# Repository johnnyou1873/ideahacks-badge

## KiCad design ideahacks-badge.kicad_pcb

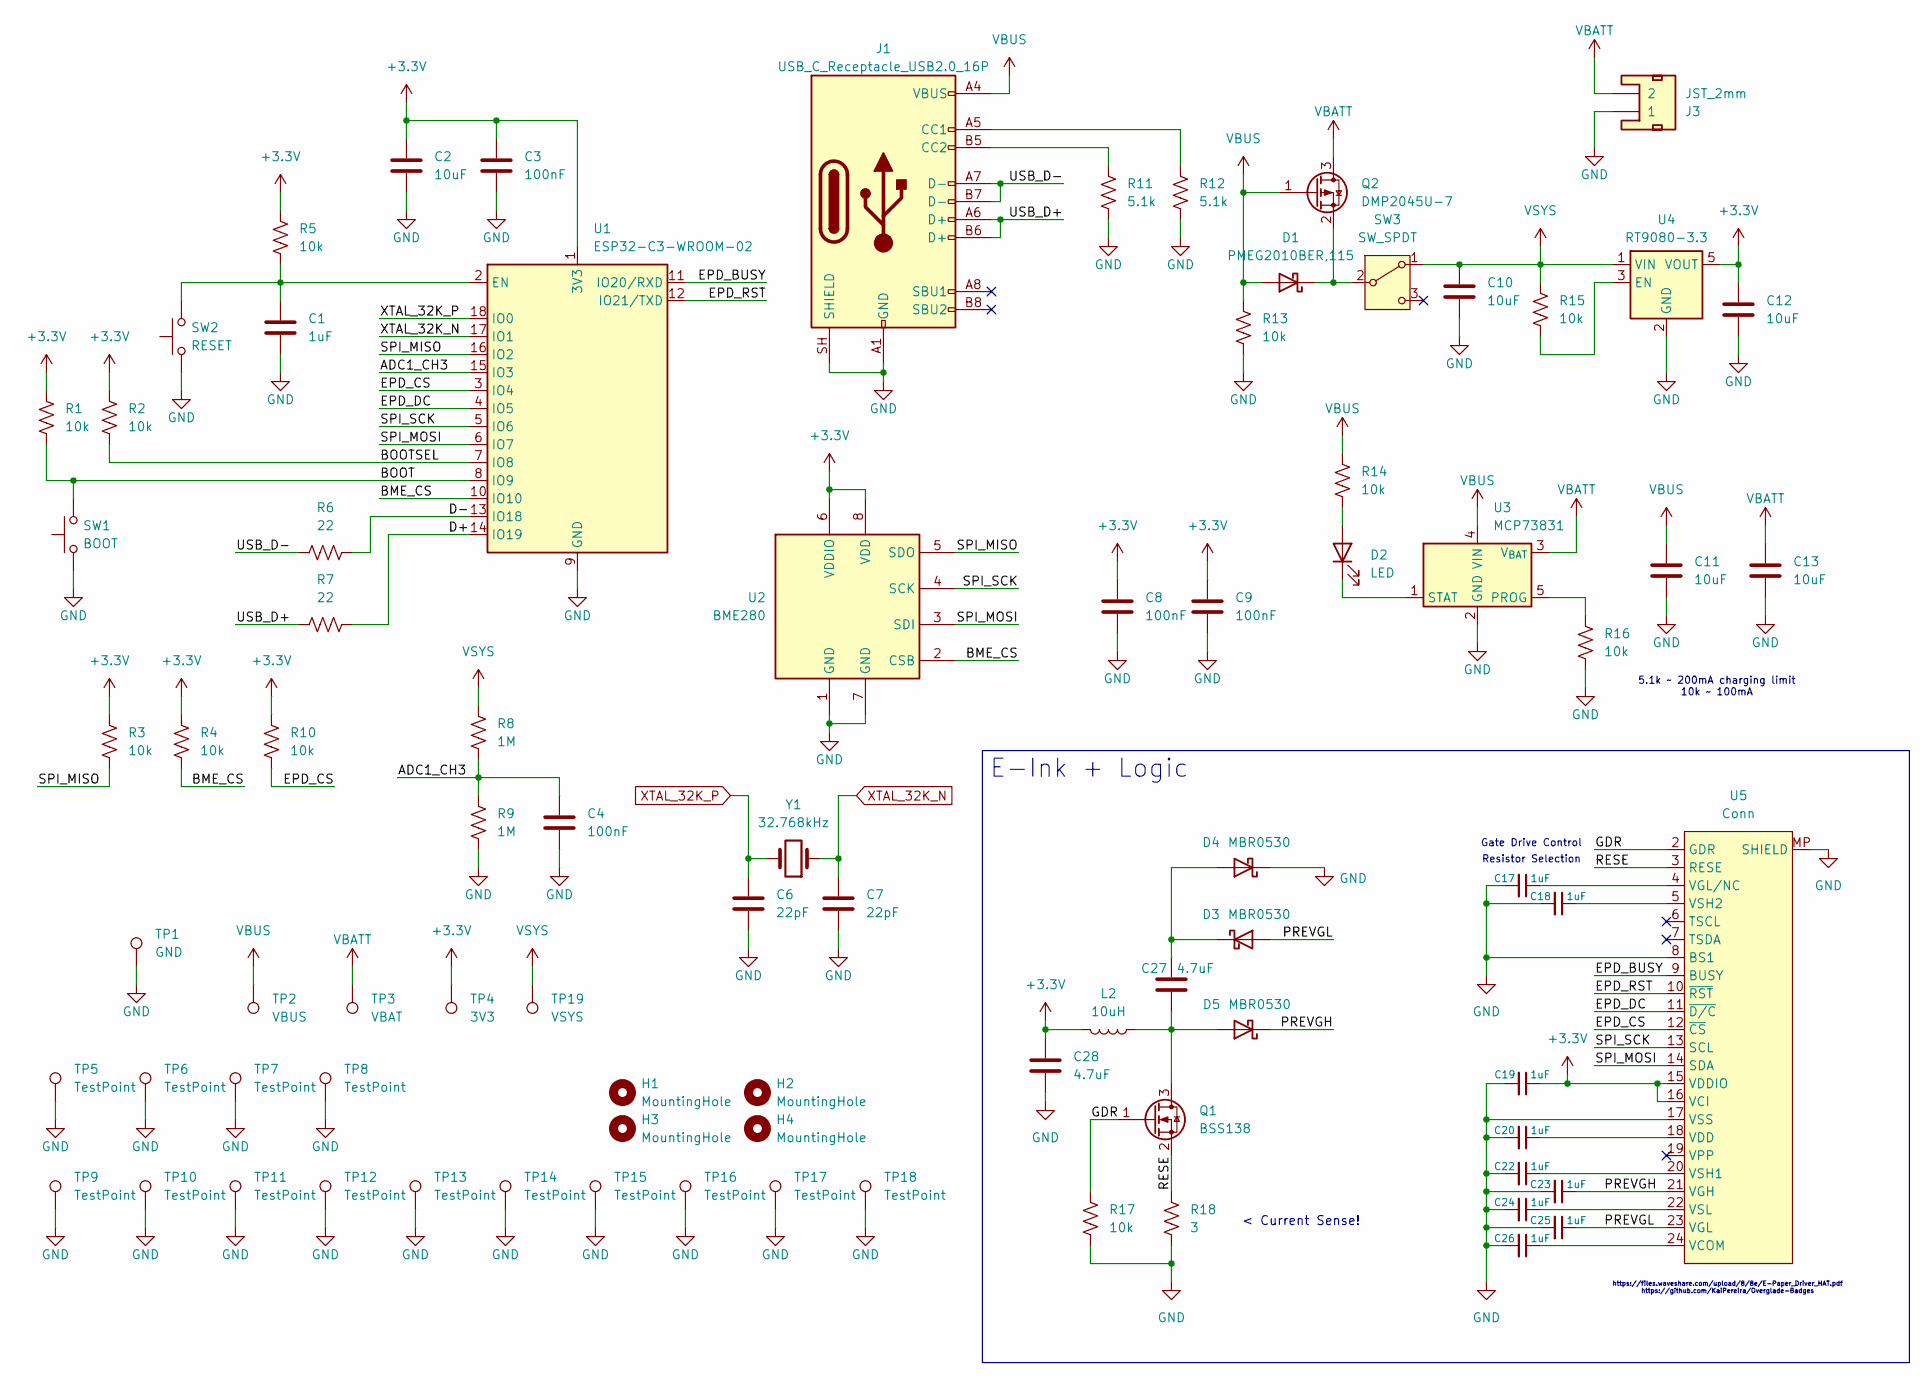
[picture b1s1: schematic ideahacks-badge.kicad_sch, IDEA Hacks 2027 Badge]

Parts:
C1, C17, C18, C19, C20, C22, C23, C24, C25, C26: 1uF; C_0805_2012Metric_Pad1.18x1.45mm_HandSolder
C2, C10, C11, C12, C13: 10uF; C_0805_2012Metric_Pad1.18x1.45mm_HandSolder
C3, C4, C8, C9: 100nF; C_0805_2012Metric_Pad1.18x1.45mm_HandSolder
C6, C7: 22pF; C_0805_2012Metric_Pad1.18x1.45mm_HandSolder
C27, C28: 4.7uF; C_0805_2012Metric_Pad1.18x1.45mm_HandSolder
D1: PMEG2010BER,115; Nexperia_CFP3_SOD-123W
D2: LED; LED_0805_2012Metric_Pad1.15x1.40mm_HandSolder
D3, D4, D5: MBR0530; D_SOD-123
H1, H2, H3, H4: MountingHole; MountingHole_3.2mm_M3_Pad
J1: USB_C_Receptacle_USB2.0_16P; USB_C_Receptacle_HRO_TYPE-C-31-M-12
J3: JST_2mm; JST_1x02_P2.0mm_Horizontal_PTH
L2: 10uH; L_Changjiang_FNR6028S; MPN FNR6028S680MT
Q1: BSS138; SOT-23_Handsoldering
Q2: DMP2045U-7; SOT-23_Handsoldering
R1, R2, R3, R4, R5, R10, R13, R14, R15, R16, R17: 10k; R_0805_2012Metric_Pad1.20x1.40mm_HandSolder
R6, R7: 22; R_0805_2012Metric_Pad1.20x1.40mm_HandSolder
R8, R9: 1M; R_0805_2012Metric_Pad1.20x1.40mm_HandSolder
R11, R12: 5.1k; R_0805_2012Metric_Pad1.20x1.40mm_HandSolder
R18: 3; R_0805_2012Metric_Pad1.20x1.40mm_HandSolder
SW1: BOOT; SW_PUSH_6mm
SW2: RESET; SW_PUSH_6mm
SW3: SW_SPDT; SW_SLW-864574-5A-RA-N-D
TP1: GND; TestPoint_Pad_D2.0mm
TP2: VBUS; TestPoint_Pad_D2.0mm
TP3: VBAT; TestPoint_Pad_D2.0mm
TP4: 3V3; TestPoint_Pad_D2.0mm
TP5, TP6, TP7, TP8, TP9, TP10, TP11, TP12, TP13, TP14, TP15, TP16, TP17, TP18: TestPoint; TestPoint_Pad_D2.0mm
TP19: VSYS; TestPoint_Pad_D2.0mm
U1: ESP32-C3-WROOM-02
U2: BME280; Bosch_LGA-8_2.5x2.5mm_P0.65mm_ClockwisePinNumbering
U3: MCP73831; SOT23-5
U4: RT9080-3.3; SOT23-5
U5: Conn; Amphenol_F32Q-1A7x1-11024_1x24-1MP_P0.5mm_Horizontal; LCSC Part # C262567
Y1: 32.768kHz; Crystal_C26-LF_D2.1mm_L6.5mm_Horizontal

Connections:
+3.3V: C2.1, C3.1, C8.1, C9.1, C12.1, C19.1, C28.2, L2.2, R1.1, R2.2, R3.1, R4.2, R5.2, R10.2, TP4.1 (1_1), U1.1 (3V3), U2.6 (VDDIO), U2.8 (VDD), U4.5 (VOUT), U5.15 (VDDIO), U5.16 (VCI)
/ADC1_CH3: C4.2, R8.2, R9.2, U1.15 (IO3)
/BME_CS: R4.1, U1.10 (IO10), U2.2 (CSB)
/BOOT: R1.2, SW1.2, U1.8 (IO9)
/BOOTSEL: R2.1, U1.7 (IO8)
/D+: R7.1, U1.14 (IO19)
/D-: R6.1, U1.13 (IO18)
/EPD_BUSY: U1.11 (IO20/RXD), U5.9 (BUSY)
/EPD_CS: R10.1, U1.3 (IO4), U5.12 (~CS)
/EPD_DC: U1.4 (IO5), U5.11 (~D/C)
/EPD_RST: U1.12 (IO21/TXD), U5.10 (~RST)
/GDR: Q1.1 (G), R17.1, U5.2 (GDR)
/PREVGH: C23.1, D5.1 (K), U5.21 (VGH)
/PREVGL: C25.1, D3.2 (A), U5.23 (VGL)
/RESE: Q1.2 (S), R18.1, U5.3 (RESE)
/SPI_MISO: R3.2, U1.16 (IO2), U2.5 (SDO)
/SPI_MOSI: U1.6 (IO7), U2.3 (SDI), U5.14 (SDA)
/SPI_SCK: U1.5 (IO6), U2.4 (SCK), U5.13 (SCL)
/USB_D+: J1.A6 (D+), J1.B6 (D+), R7.2
/USB_D-: J1.A7 (D-), J1.B7 (D-), R6.2
GND: C1.2, C2.2, C3.2, C4.1, C6.1, C7.1, C8.2, C9.2, C10.2, C11.2, C12.2, C13.2, C17.2, C18.2, C19.2, C20.2, C22.2, C23.2, C24.2, C25.2, C26.2, C28.1, D4.1 (K), J1.A1 (GND), J1.A12 (GND), J1.B1 (GND), J1.B12 (GND), J1.SH (SHIELD), J3.1, R9.1, R11.2, R12.2, R13.2, R16.2, R17.2, R18.2, SW1.1, SW2.1, TP1.1 (1_1), TP5.1 (1_1), TP6.1 (1_1), TP7.1 (1_1), TP8.1 (1_1), TP9.1 (1_1), TP10.1 (1_1), TP11.1 (1_1), TP12.1 (1_1), TP13.1 (1_1), TP14.1 (1_1), TP15.1 (1_1), TP16.1 (1_1), TP17.1 (1_1), TP18.1 (1_1), U1.9 (GND), U1.19 (GND), U2.1 (GND), U2.7 (GND), U3.2 (GND), U4.2 (GND), U5.8 (BS1), U5.17 (VSS), U5.MP (SHIELD)
unnamed: D1.1 (K), Q2.2 (S), SW3.2 (B)
unnamed: D2.2 (A), R14.2
unnamed: D2.1 (K), U3.1 (STAT)
unnamed: C27.2, D3.1 (K), D4.2 (A)
unnamed: C27.1, D5.2 (A), L2.1, Q1.3 (D)
unnamed: J1.A5 (CC1), R12.1
unnamed: J1.B5 (CC2), R11.1
unnamed: C1.1, R5.1, SW2.2, U1.2 (EN)
unnamed: R16.1, U3.5 (PROG)
unnamed: R15.2, U4.3 (EN)
unnamed: C26.1, U5.24 (VCOM)
unnamed: C20.1, U5.18 (VDD)
unnamed: C17.1, U5.4 (VGL/NC)
unnamed: C22.1, U5.20 (VSH1)
unnamed: C18.1, U5.5 (VSH2)
unnamed: C24.1, U5.22 (VSL)
VBATT: C13.1, J3.2, Q2.3 (D), TP3.1 (1_1), U3.3 (V_{BAT})
VBUS: C11.1, D1.2 (A), J1.A4 (VBUS), J1.A9 (VBUS), J1.B4 (VBUS), J1.B9 (VBUS), Q2.1 (G), R13.1, R14.1, TP2.1 (1_1), U3.4 (VIN)
VSYS: C10.1, R8.1, R15.1, SW3.1 (A), TP19.1 (1_1), U4.1 (VIN)
XTAL_32K_N: C7.2, U1.17 (IO1), Y1.1
XTAL_32K_P: C6.2, U1.18 (IO0), Y1.2

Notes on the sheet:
5.1k ~ 200mA charging limit 10k ~ 100mA
https://files.waveshare.com/upload/8/8e/E-Paper_Driver_HAT.pdf https://github.com/KaiPereira/Overglade-Badges
Resistor Selection
Gate Drive Control
< Current Sense!
E-Ink + Logic

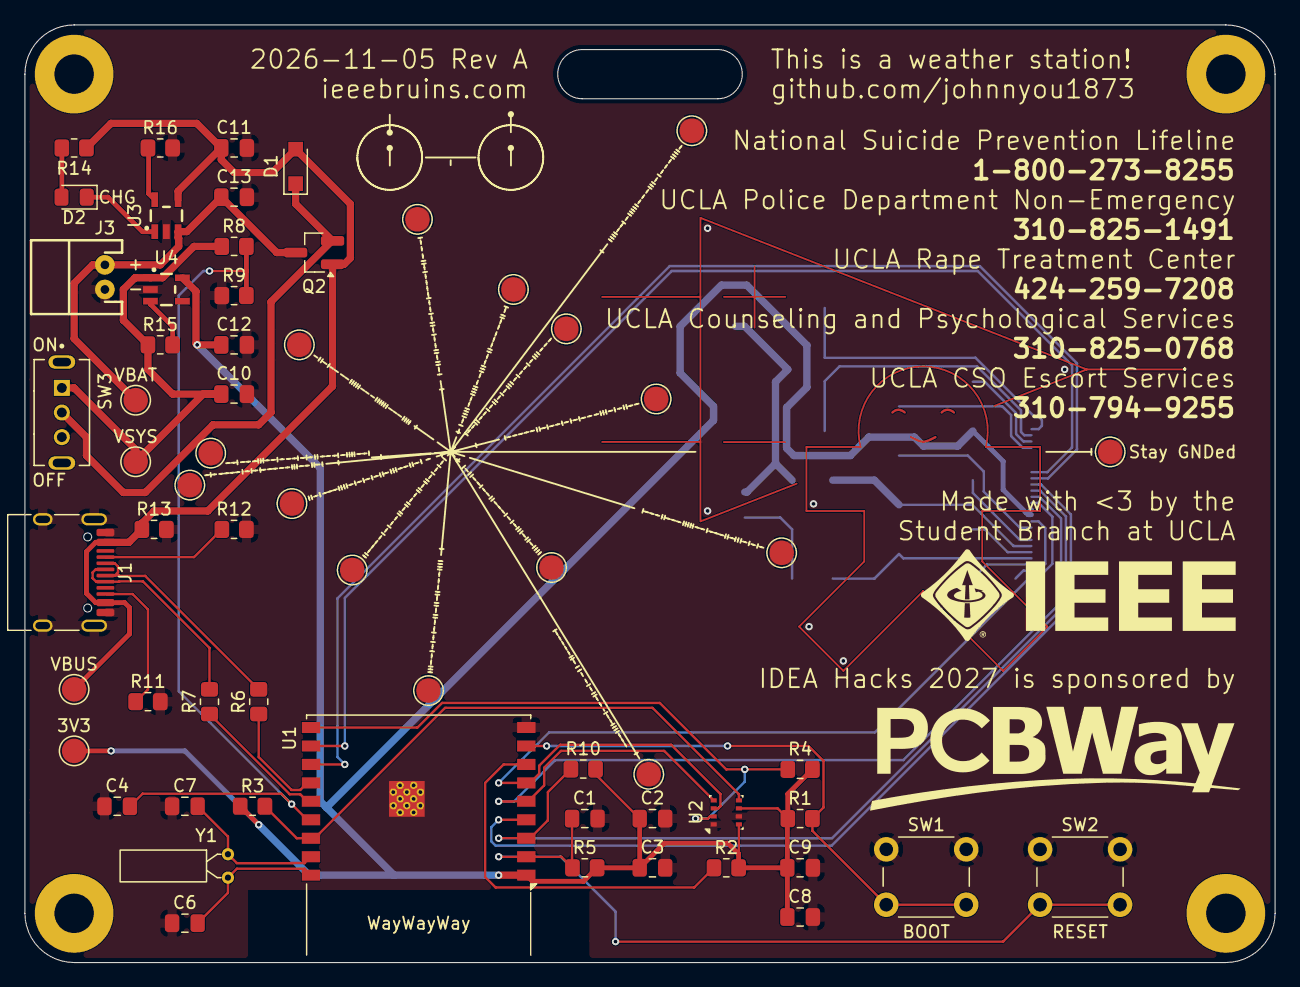
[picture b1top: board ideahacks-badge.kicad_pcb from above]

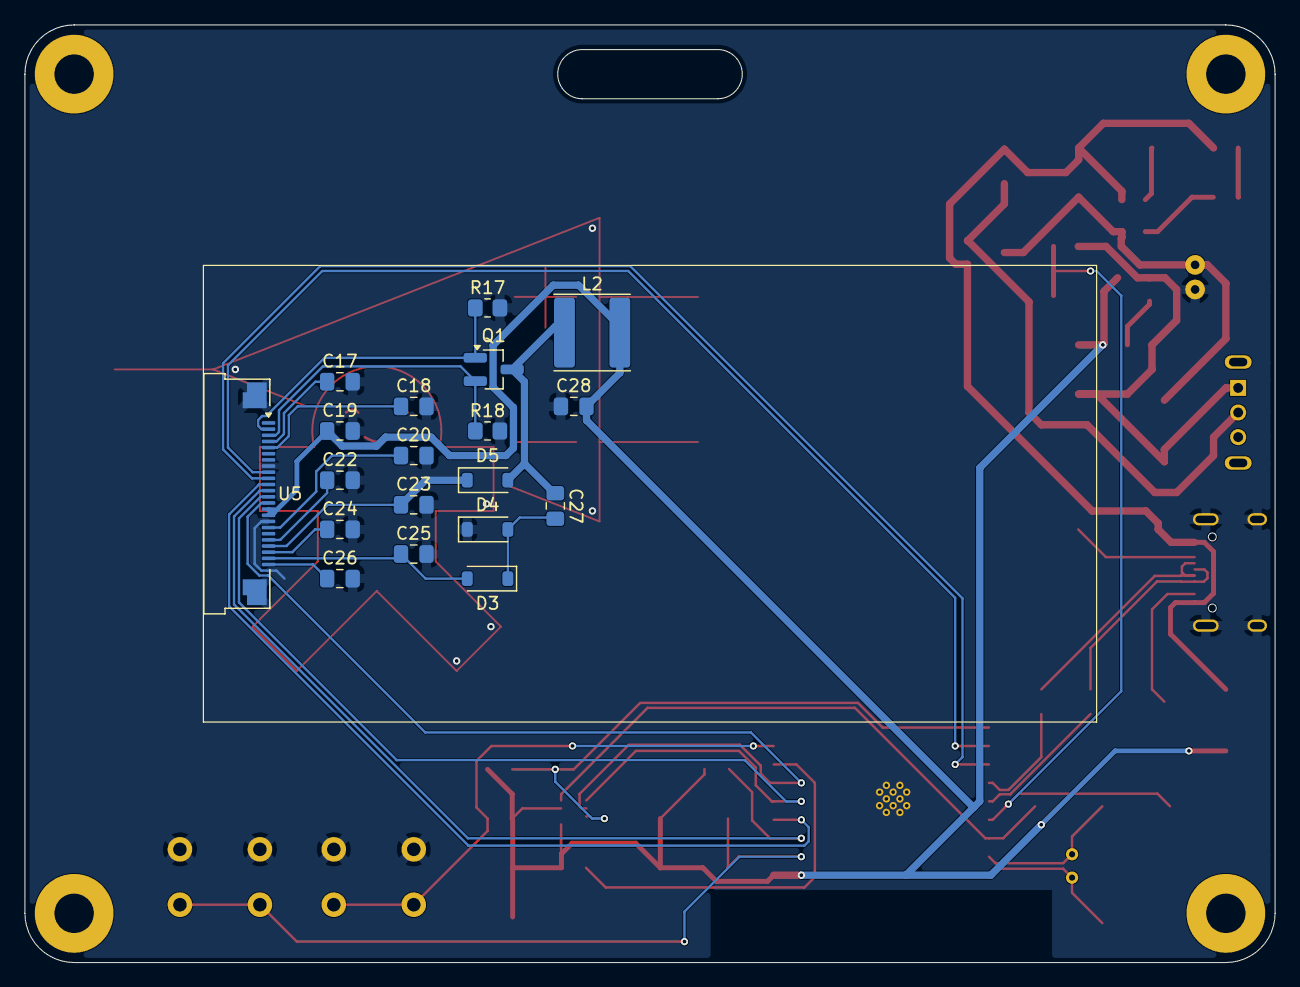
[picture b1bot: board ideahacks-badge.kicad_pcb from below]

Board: 2 copper layers, 101.6 x 76.2 mm, 83 parts (19 on the bottom side), 42 nets.
